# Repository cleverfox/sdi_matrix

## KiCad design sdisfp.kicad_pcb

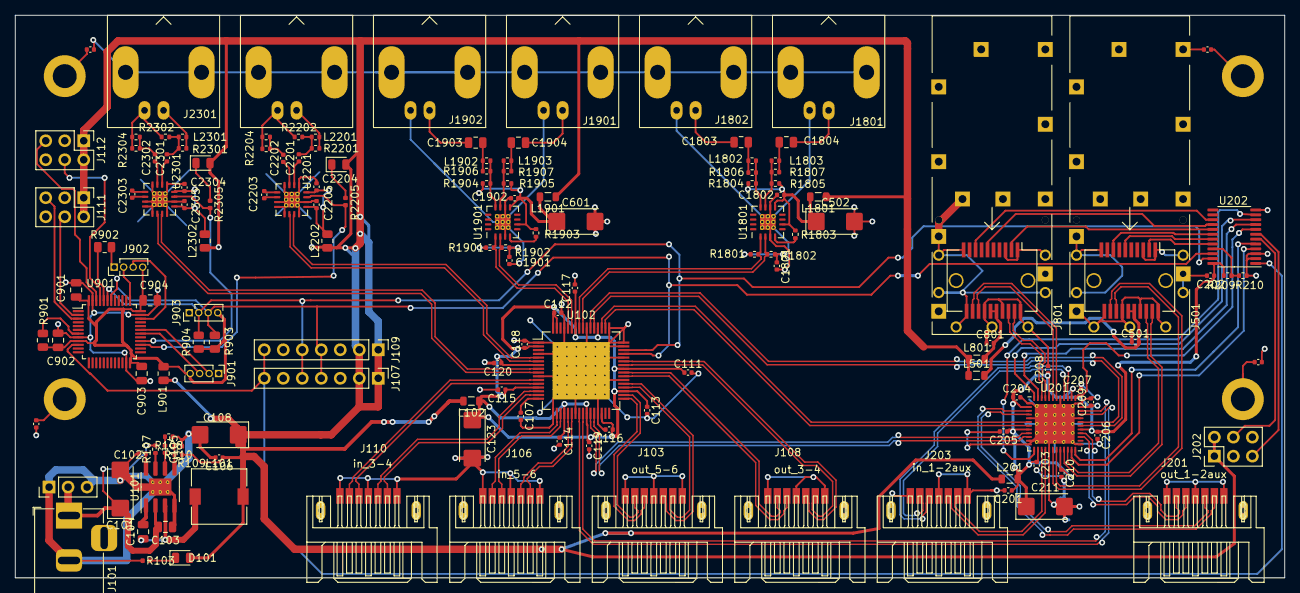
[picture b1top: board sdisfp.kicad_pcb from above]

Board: 2 copper layers, 169.7 x 75.2 mm, 151 parts (0 on the bottom side), 135 nets.

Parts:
C101: C_Polarized_Small; CP_EIA-6032-20_AVX-F_Pad2.25x2.35mm_HandSolder
C102, C106, C107, C111, C112, C113, C114, C115, C116, C117, C118, C119, C120, C203, C204, C205, C206, C207, C208, C209, C210, C501, C801, C1801, C1802, C1901, C1902, C2204, C2205, C2304, C2305: 0.1uF; C_0402_1005Metric
C103: C_Small; C_0805_2012Metric
C104: 10nF; C_0805_2012Metric
C105: 3.9nF; C_0402_1005Metric
C108, C123, C211, C502, C601: 47uF; CP_EIA-6032-20_AVX-F_Pad2.25x2.35mm_HandSolder
C109, C110, C121, C122: C; C_0402_1005Metric
C201, C202: C_Small; C_0402_1005Metric
C901, C902, C903, C904: 0.1uF; C_0805_2012Metric
C1803, C1804, C1903, C1904: 4.7uF; C_0805_2012Metric
C2201, C2202, C2203, C2301, C2302, C2303: 1uF; C_0402_1005Metric
D101: pwr; LED_0805_2012Metric
D2201, D2301: IN_CD; LED_0805_2012Metric
J101: Jack-DC; BarrelJack_Horizontal
J102: Conn_01x03; PinHeader_1x03_P2.54mm_Vertical
J103: out_5-6; SATA-7_SMD
J104, J105, J113, J114: mounting_hole; MountingHole_3.2mm_M3_DIN965_Pad
J106: in_5-6; SATA-7_SMD
J107, J109: ext1; PinHeader_1x07_P2.54mm_Vertical
J108: out_3-4; SATA-7_SMD
J110: in_3-4; SATA-7_SMD
J111: in_5-6aux_pwr; PinHeader_2x03_P2.54mm_Vertical
J112: in_3-4aux_pwr; PinHeader_2x03_P2.54mm_Vertical
J201: out_1-2aux; SATA-7_SMD
J202: in_1-2aux_pwr; PinHeader_2x03_P2.54mm_Vertical
J203: in_1-2aux; SATA-7_SMD
J501: SFP1; Connector_SFP_and_Cage
J801: SFP2; Connector_SFP_and_Cage
J901, J902: SWD; PinHeader_1x04_P1.27mm_Vertical
J903: I2C; PinHeader_1x04_P1.27mm_Vertical
J1801: OUTn7; BNC_Amphenol_B6252HB-NPP3G-50_Horizontal
J1802: OUTp7; BNC_Amphenol_B6252HB-NPP3G-50_Horizontal
J1901: OUTn8; BNC_Amphenol_B6252HB-NPP3G-50_Horizontal
J1902: OUTp8; BNC_Amphenol_B6252HB-NPP3G-50_Horizontal
J2201: IN7; BNC_Amphenol_B6252HB-NPP3G-50_Horizontal
J2301: IN8; BNC_Amphenol_B6252HB-NPP3G-50_Horizontal
L101: 10uH; L_7.3x7.3_H3.5
L102, L201, L501, L801, L1801, L1901: L; L_0805_2012Metric
L901: L; R_0805_2012Metric
L1802, L1803, L1902, L1903, L2201, L2301: 3.9nH; R_0402_1005Metric
L2202, L2302: bead; R_0805_2012Metric
R103, R2205, R2305: 1k; L_0402_1005Metric
R107: 100k; R_0402_1005Metric
R108: 6k8; R_0402_1005Metric
R109: 39k; R_0402_1005Metric
R110: 15k; R_0402_1005Metric
R209: 0; R_0402_1005Metric
R210, R2203, R2303: -; R_0402_1005Metric
R901: R_Small; R_0805_2012Metric
R902: 0; R_0805_2012Metric
R903, R904: 1k; R_0805_2012Metric
R1801, R1802, R1901, R1902: 50; R_0402_1005Metric
R1803, R1903: 750; R_0402_1005Metric
R1804, R1805, R1806, R1807, R1904, R1905, R1906, R1907, R2201, R2202, R2301, R2302: 75; R_0402_1005Metric
R2204, R2304: 37.4; R_0402_1005Metric
U101: MP2307; SOIC-8-1EP_3.9x4.9mm_P1.27mm_EP2.29x3mm_ThermalVias
U102: SN65LVCP408PAPR; TQFP-64-1EP_10x10mm_P0.5mm_EP8x8mm
U201: DS42MB200; QFN-48-1EP_7x7mm_P0.5mm_EP5.3x5.3mm_ThermalVias
U202: PCA9675PW,118; TSSOP-24_4.4x7.8mm_P0.65mm
U901: STM32F100C8Tx; LQFP-48_7x7mm_P0.5mm
U1801, U1901: LMH0303; QFN-16-1EP_4x4mm_P0.65mm_EP2.1x2.1mm_ThermalVias
U2201, U2301: LMH0344; QFN-16-1EP_4x4mm_P0.65mm_EP2.1x2.1mm_ThermalVias

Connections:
+3V3: C106.1, C108.1, D101.2, D2201.2, D2301.2, J107.1, J107.2, J109.1, J109.2, J111.1, J111.2, J112.1, J112.2, J202.1, J202.2, L101.2, L102.2, L201.1, L501.1, L801.1, L901.1, L1801.1, L1901.1, L2202.1, L2302.1, R109.2
/CD3: J112.4, U901.45
/CD4: J112.5, U901.46
/CD5: J111.4, U901.2
/CD6: J111.5, U901.3
/CD7: R2205.2, U901.27, U2201.15
/CD8: R2305.2, U901.28, U2301.15
/INT: J107.7, J109.7, U202.1, U901.10
/MCU/JTCK: J902.2, U901.37
/MCU/JTMS: J902.3, U901.34
/MCU/MCU_VCC: C901.1, C902.1, C903.1, C904.1, J901.4, J902.4, J903.4, L901.2, R901.1, R903.1, R904.1, U901.9, U901.24, U901.36, U901.48
/MCU/RX: J901.2, U901.31
/MCU/TX: J901.3, U901.30
/MTX_VCC: C111.1, C112.1, C113.1, C114.1, C115.1, C116.1, C117.1, C118.1, C119.1, C120.1, C123.1, L102.1, U102.2, U102.7, U102.13, U102.20, U102.26, U102.30, U102.35, U102.41, U102.52, U102.58, U102.63, U102.64
/P1RX+: U102.27, U201.9
/P1RX-: U102.28, U201.10
/P1TX+: U102.54, U201.30
/P1TX-: U102.53, U201.31
/P2RX+: U102.24, U201.33
/P2RX-: U102.25, U201.34
/P2TX+: U102.51, U201.6
/P2TX-: U102.50, U201.7
/P3RX+: J110.2, U102.11
/P3RX-: J110.3, U102.12
/P3TX+: J108.2, U102.40
/P3TX-: J108.3, U102.39
/P4RX+: J110.5, U102.14
/P4RX-: J110.6, U102.15
/P4TX+: J108.5, U102.43
/P4TX-: J108.6, U102.42
/P5RX+: J106.2, U102.18
/P5RX-: J106.3, U102.19
/P5TX+: J103.2, U102.34
/P5TX-: J103.3, U102.33
/P6RX+: J106.5, U102.21
/P6RX-: J106.6, U102.22
/P6TX+: J103.5, U102.37
/P6TX-: J103.6, U102.36
/P7RX+: U102.5, U2201.11
/P7RX-: U102.6, U2201.10
/P7TX+: R1801.2, U102.57, U1801.1
/P7TX-: R1802.1, U102.56, U1801.2
/P8RX+: U102.8, U2301.11
/P8RX-: U102.9, U2301.10
/P8TX+: R1901.2, U102.60, U1901.1
/P8TX-: R1902.1, U102.59, U1901.2
/Ports 1-2/M1VCC: C201.1, C202.1, C203.1, C204.1, C205.1, C206.1, C207.1, C208.1, C209.1, C210.1, C211.1, L201.2, R209.1, U201.2, U201.8, U201.14, U201.20, U201.29, U201.35, U201.38, U201.44, U202.24
/Ports 1-2/MUX_LB0A: U201.47, U202.9
/Ports 1-2/MUX_LB0B: U201.48, U202.10
/Ports 1-2/MUX_LB1A: U201.23, U202.4
/Ports 1-2/MUX_LB1B: U201.24, U202.5
/Ports 1-2/MUX_S0: U201.37, U202.8
/Ports 1-2/MUX_S1: U201.13, U202.11
/Ports 1-2/P1RX+: J203.5, U201.16
/Ports 1-2/P1RX-: J203.6, U201.15
/Ports 1-2/P1TX+: J201.2, U201.28
/Ports 1-2/P1TX-: J201.3, U201.27
/Ports 1-2/P2RX+: J203.2, U201.40
/Ports 1-2/P2RX-: J203.3, U201.39
/Ports 1-2/P2TX+: J201.5, U201.4
/Ports 1-2/P2TX-: J201.6, U201.3
/Ports 1-2/SFP1/RX+: J501.13, U201.19
/Ports 1-2/SFP1/RX-: J501.12, U201.18
/Ports 1-2/SFP1/TX+: J501.18, U201.22
/Ports 1-2/SFP1/TX-: J501.19, U201.21
/Ports 1-2/SFP1FAULT: J501.2, U202.20
/Ports 1-2/SFP1LOS: J501.8, U202.18
/Ports 1-2/SFP1PRES: J501.6, U202.19
/Ports 1-2/SFP2/RX+: J801.13, U201.43
/Ports 1-2/SFP2/RX-: J801.12, U201.42
/Ports 1-2/SFP2/TX+: J801.18, U201.46
/Ports 1-2/SFP2/TX-: J801.19, U201.45
/Ports 1-2/SFP2FAULT: J801.2, U202.17
/Ports 1-2/SFP2LOS: J801.8, U202.15
/Ports 1-2/SFP2PRES: J801.6, U202.16
/Ports 1-2/in1_cd: J202.5, U202.7
/Ports 1-2/in2_cd: J202.4, U202.6
/SCL: J107.4, J109.4, J903.3, R903.2, U102.45, U202.22, U901.42
/SDA: J107.5, J109.5, J903.2, R904.2, U102.46, U202.23, U901.43
/SDI Out 7/CD_VCC: C502.1, C1802.2, L1801.2, R1803.2, R1804.1, R1805.1, U1801.6, U1801.9
/SDI Out 7/SDO+: L1802.1, R1804.2, R1806.2, U1801.12
/SDI Out 7/SDO-: L1803.2, R1805.2, R1807.2, U1801.11
/SDI Out 8/CD_VCC: C601.1, C1902.2, L1901.2, R1903.2, R1904.1, R1905.1, U1901.6, U1901.9
/SDI Out 8/SDO+: L1902.1, R1904.2, R1906.2, U1901.12
/SDI Out 8/SDO-: L1903.2, R1905.2, R1907.2, U1901.11
GND: C101.2, C102.2, C103.2, C106.2, C107.2, C108.2, C109.2, C110.2, C111.2, C112.2, C113.2, C114.2, C115.2, C116.2, C117.2, C118.2, C119.2, C120.2, C121.2, C122.2, C123.2, C201.2, C202.2, C203.2, C204.2, C205.2, C206.2, C207.2, C208.2, C209.2, C210.2, C211.2, C501.1, C502.2, C601.2, C801.1, C901.2, C902.2, C903.2, C904.2, C1801.2, C1802.1, C1901.2, C1902.1, C2204.2, C2205.2, C2304.2, C2305.2, J101.2, J102.1, J102.3, J103.1, J103.4, J103.7, J106.1, J106.4, J106.7, J107.3, J107.6, J108.1, J108.4, J108.7, J109.3, J109.6, J110.1, J110.4, J110.7, J111.3, J111.6, J112.3, J112.6, J201.1, J201.4, J201.7, J202.3, J202.6, J203.1, J203.4, J203.7, J501.1, J501.3, J501.10, J501.11, J501.14, J501.17, J501.20, J501.CAGE, J801.1, J801.3, J801.10, J801.11, J801.14, J801.17, J801.20, J801.CAGE, J901.1, J902.1, J903.1, J1801.2, J1802.2, J1901.2, J1902.2, J2201.2, J2301.2, R103.2, R108.1, R110.1, R210.2, R902.2, R2202.2, R2203.1, R2204.2, R2302.2, R2303.1, R2304.2, U101.4, U101.9, U102.1, U102.4, U102.10, U102.17, U102.23, U102.29, U102.38, U102.44, U102.47, U102.48, U102.49, U102.55, U102.61, U102.65, U201.1, U201.5, U201.11, U201.12, U201.17, U201.25, U201.32, U201.36, U201.41, U201.49, U202.2, U202.3, U202.12, U901.8, U901.23, U901.35, U901.47, U1801.3, U1801.10, U1801.17, U1901.3, U1901.10, U1901.17, U2201.1, U2201.4, U2201.7, U2201.8, U2201.9, U2201.12, U2201.14, U2201.17, U2301.1, U2301.4, U2301.7, U2301.8, U2301.9, U2301.12, U2301.14, U2301.17
unnamed: C101.1, C103.1, J101.1, J102.2, R107.2, U101.2
unnamed: C102.1, U101.8
unnamed: C104.1, L101.1, U101.3
unnamed: C104.2, U101.1
unnamed: C105.1, R108.2
unnamed: C105.2, U101.6
unnamed: C107.1, U102.16
unnamed: C109.1, J104.1
unnamed: C110.1, J105.1
unnamed: C121.1, J113.1
unnamed: C122.1, J114.1
unnamed: C501.2, J501.15, J501.16, L501.2
unnamed: C801.2, J801.15, J801.16, L801.2
unnamed: C1801.1, R1801.1, R1802.2
unnamed: C1803.1, L1802.2, R1806.1
unnamed: C1803.2, J1802.1
unnamed: C1804.1, L1803.1, R1807.1
unnamed: C1804.2, J1801.1
unnamed: C1901.1, R1901.1, R1902.2
unnamed: C1903.1, L1902.2, R1906.1
unnamed: C1903.2, J1902.1
unnamed: C1904.1, L1903.1, R1907.1
unnamed: C1904.2, J1901.1
unnamed: C2201.1, U2201.2
unnamed: C2201.2, L2201.2, R2201.1, R2202.1
unnamed: C2202.1, U2201.3
unnamed: C2202.2, R2203.2, R2204.1
unnamed: C2203.1, U2201.5
unnamed: C2203.2, U2201.6
unnamed: C2204.1, C2205.1, L2202.2, U2201.13, U2201.16
unnamed: C2301.1, U2301.2
unnamed: C2301.2, L2301.2, R2301.1, R2302.1
unnamed: C2302.1, U2301.3
unnamed: C2302.2, R2303.2, R2304.1
unnamed: C2303.1, U2301.5
unnamed: C2303.2, U2301.6
unnamed: C2304.1, C2305.1, L2302.2, U2301.13, U2301.16
unnamed: D101.1, R103.1
unnamed: D2201.1, R2205.1
unnamed: D2301.1, R2305.1
unnamed: J2201.1, L2201.1, R2201.2
unnamed: J2301.1, L2301.1, R2301.2
unnamed: R107.1, U101.7
unnamed: R109.1, R110.2, U101.5
unnamed: R209.2, R210.1, U202.21
unnamed: R901.2, U901.7
unnamed: R902.1, U901.44
unnamed: R1803.1, U1801.4
unnamed: R1903.1, U1901.4

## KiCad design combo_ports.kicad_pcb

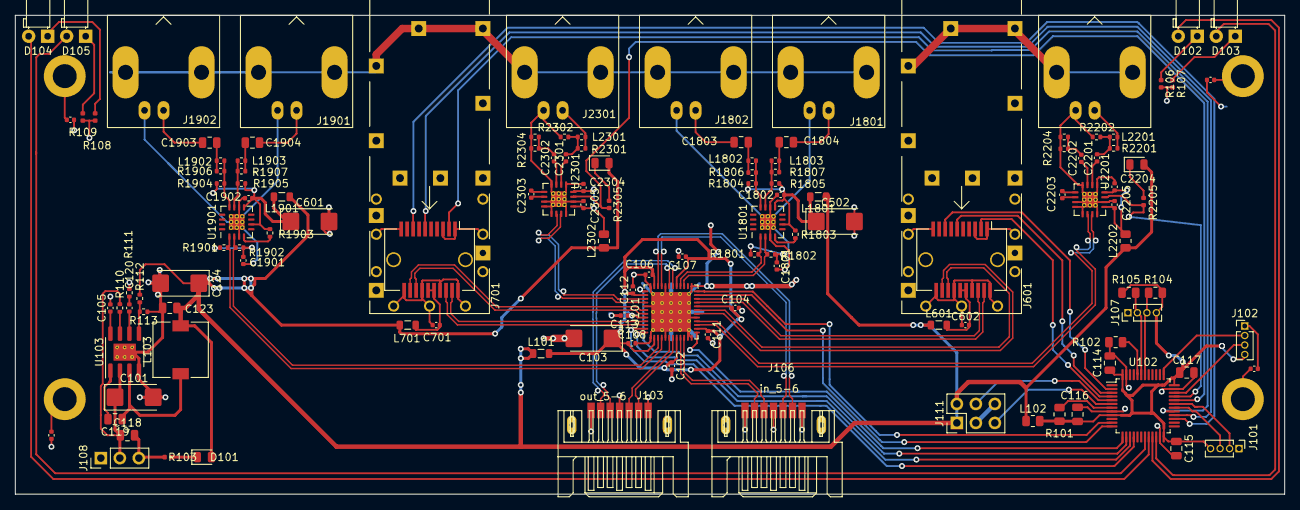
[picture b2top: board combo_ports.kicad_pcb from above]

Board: 2 copper layers, 169.7 x 64.0 mm, 131 parts (0 on the bottom side), 111 nets.

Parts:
C101: C_Polarized_Small; CP_EIA-6032-20_AVX-F_Pad2.25x2.35mm_HandSolder
C102, C104, C105, C106, C107, C108, C111, C602, C701, C1801, C1802, C1901, C1902, C2204, C2205, C2304, C2305: 0.1uF; C_0402_1005Metric
C103, C124, C502, C601: 47uF; CP_EIA-6032-20_AVX-F_Pad2.25x2.35mm_HandSolder
C109, C110, C121, C122: C; C_0402_1005Metric
C112, C113: C_Small; C_0402_1005Metric
C114, C115, C116, C117, C123: 0.1uF; C_0805_2012Metric
C118: C_Small; C_0805_2012Metric
C119: 10nF; C_0805_2012Metric
C120: 3.9nF; C_0402_1005Metric
C1803, C1804, C1903, C1904: 4.7uF; C_0805_2012Metric
C2201, C2202, C2203, C2301, C2302, C2303: 1uF; C_0402_1005Metric
D101: pwr; LED_0805_2012Metric
D102: P2SFP; LED_D3.0mm_Horizontal_O1.27mm_Z2.0mm
D103: P2SDI; LED_D3.0mm_Horizontal_O1.27mm_Z2.0mm
D104: P1SFP; LED_D3.0mm_Horizontal_O1.27mm_Z2.0mm
D105: P1SDI; LED_D3.0mm_Horizontal_O1.27mm_Z2.0mm
D2201, D2301: IN_CD; LED_0805_2012Metric
J101, J102: SWD; PinHeader_1x04_P1.27mm_Vertical
J103: out_5-6; SATA-7_SMD
J104, J105, J113, J114: mounting_hole; MountingHole_3.2mm_M3_DIN965_Pad
J106: in_5-6; SATA-7_SMD
J107: I2C; PinHeader_1x04_P1.27mm_Vertical
J108: Conn_01x03; PinHeader_1x03_P2.54mm_Vertical
J111: in_5-6aux_pwr; PinHeader_2x03_P2.54mm_Vertical
J601: SFP1; Connector_SFP_and_Cage
J701: SFP2; Connector_SFP_and_Cage
J1801: OUTn7; BNC_Amphenol_B6252HB-NPP3G-50_Horizontal
J1802: OUTp7; BNC_Amphenol_B6252HB-NPP3G-50_Horizontal
J1901: OUTn8; BNC_Amphenol_B6252HB-NPP3G-50_Horizontal
J1902: OUTp8; BNC_Amphenol_B6252HB-NPP3G-50_Horizontal
J2201: IN7; BNC_Amphenol_B6252HB-NPP3G-50_Horizontal
J2301: IN8; BNC_Amphenol_B6252HB-NPP3G-50_Horizontal
L101, L601, L701, L1801, L1901: L; L_0805_2012Metric
L102: L; R_0805_2012Metric
L103: 10uH; L_7.3x7.3_H3.5
L1802, L1803, L1902, L1903, L2201, L2301: 3.9nH; R_0402_1005Metric
L2202, L2302: bead; R_0805_2012Metric
R101: R_Small; R_0805_2012Metric
R102: 0; R_0805_2012Metric
R103, R106, R107, R108, R109, R2205, R2305: 1k; L_0402_1005Metric
R104, R105: 1k; R_0805_2012Metric
R110: 100k; R_0402_1005Metric
R111: 6k8; R_0402_1005Metric
R112: 39k; R_0402_1005Metric
R113: 15k; R_0402_1005Metric
R1801, R1802, R1901, R1902: 50; R_0402_1005Metric
R1803, R1903: 750; R_0402_1005Metric
R1804, R1805, R1806, R1807, R1904, R1905, R1906, R1907, R2201, R2202, R2301, R2302: 75; R_0402_1005Metric
R2203, R2303: -; R_0402_1005Metric
R2204, R2304: 37.4; R_0402_1005Metric
U101: DS42MB200; QFN-48-1EP_7x7mm_P0.5mm_EP5.3x5.3mm_ThermalVias
U102: STM32F100C8Tx; LQFP-48_7x7mm_P0.5mm
U103: MP2307; SOIC-8-1EP_3.9x4.9mm_P1.27mm_EP2.29x3mm_ThermalVias
U1801, U1901: LMH0303; QFN-16-1EP_4x4mm_P0.65mm_EP2.1x2.1mm_ThermalVias
U2201, U2301: LMH0344; QFN-16-1EP_4x4mm_P0.65mm_EP2.1x2.1mm_ThermalVias

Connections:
+3V3: C123.1, C124.1, D101.2, D2201.2, D2301.2, J111.1, J111.2, L101.1, L102.1, L103.2, L601.1, L701.1, L1801.1, L1901.1, L2202.1, L2302.1, R112.2
/CD5: R2205.2, U102.33, U2201.15
/CD6: R2305.2, U102.32, U2301.15
/JTCK: J102.2, U102.37
/JTMS: J102.3, U102.34
/M1VCC: C102.1, C103.1, C104.1, C106.1, C107.1, C108.1, C111.1, C112.1, C113.1, L101.2, U101.2, U101.8, U101.14, U101.20, U101.29, U101.35, U101.38, U101.44
/MCD5: J111.4, U102.5
/MCD6: J111.5, U102.6
/MCU_VCC: C114.1, C115.1, C116.1, C117.1, J101.4, J102.4, J107.4, L102.2, R101.1, R104.1, R105.1, U102.9, U102.24, U102.36, U102.48
/MUX_LB0A: U101.47, U102.16
/MUX_LB0B: U101.48, U102.15
/MUX_LB1A: U101.23, U102.12
/MUX_LB1B: U101.24, U102.11
/MUX_S0: U101.37, U102.14
/MUX_S1: U101.13, U102.13
/P1RX+: U101.16, U2201.11
/P1RX-: U101.15, U2201.10
/P1TX+: R1801.2, U101.28, U1801.1
/P1TX-: R1802.1, U101.27, U1801.2
/P2RX+: U101.40, U2301.11
/P2RX-: U101.39, U2301.10
/P2TX+: R1901.2, U101.4, U1901.1
/P2TX-: R1902.1, U101.3, U1901.2
/RX: J101.2, U102.31
/RX1+: J106.2, U101.9
/RX1-: J106.3, U101.10
/RX2+: J106.5, U101.33
/RX2-: J106.6, U101.34
/SCL: J107.3, R104.2, U102.42
/SDA: J107.2, R105.2, U102.43
/SDI1CD: D105.2, U102.19
/SDI2CD: D102.2, U102.21
/SDI Out 5/CD_VCC: C502.1, C1802.2, L1801.2, R1803.2, R1804.1, R1805.1, U1801.6, U1801.9
/SDI Out 5/SDO+: L1802.1, R1804.2, R1806.2, U1801.12
/SDI Out 5/SDO-: L1803.2, R1805.2, R1807.2, U1801.11
/SDI Out 6/CD_VCC: C601.1, C1902.2, L1901.2, R1903.2, R1904.1, R1905.1, U1901.6, U1901.9
/SDI Out 6/SDO+: L1902.1, R1904.2, R1906.2, U1901.12
/SDI Out 6/SDO-: L1903.2, R1905.2, R1907.2, U1901.11
/SFP1CD: D104.2, U102.20
/SFP1FAULT: J601.2, U102.4
/SFP1LOS: J601.8, U102.2
/SFP1PRES: J601.6, U102.3
/SFP2CD: D103.2, U102.22
/SFP2FAULT: J701.2, U102.29
/SFP2LOS: J701.8, U102.27
/SFP2PRES: J701.6, U102.28
/TX: J101.3, U102.30
/TX1+: J103.2, U101.30
/TX1-: J103.3, U101.31
/TX2+: J103.5, U101.6
/TX2-: J103.6, U101.7
/sfp5/RX+: J601.13, U101.19
/sfp5/RX-: J601.12, U101.18
/sfp5/SFPVCC: C602.2, J601.15, J601.16, L601.2
/sfp5/TX+: J601.18, U101.22
/sfp5/TX-: J601.19, U101.21
/sfp6/RX+: J701.13, U101.43
/sfp6/RX-: J701.12, U101.42
/sfp6/SFPVCC: C701.2, J701.15, J701.16, L701.2
/sfp6/TX+: J701.18, U101.46
/sfp6/TX-: J701.19, U101.45
GND: C101.2, C102.2, C103.2, C104.2, C105.2, C106.2, C107.2, C108.2, C109.2, C110.2, C111.2, C112.2, C113.2, C114.2, C115.2, C116.2, C117.2, C118.2, C121.2, C122.2, C123.2, C124.2, C502.2, C601.2, C602.1, C701.1, C1801.2, C1802.1, C1901.2, C1902.1, C2204.2, C2205.2, C2304.2, C2305.2, J101.1, J102.1, J103.1, J103.4, J103.7, J106.1, J106.4, J106.7, J107.1, J108.1, J108.3, J111.3, J111.6, J601.1, J601.3, J601.10, J601.11, J601.14, J601.17, J601.20, J601.CAGE, J701.1, J701.3, J701.10, J701.11, J701.14, J701.17, J701.20, J701.CAGE, J1801.2, J1802.2, J1901.2, J1902.2, J2201.2, J2301.2, R102.2, R103.2, R106.2, R107.2, R108.2, R109.2, R111.1, R113.1, R2202.2, R2203.1, R2204.2, R2302.2, R2303.1, R2304.2, U101.1, U101.5, U101.11, U101.12, U101.17, U101.25, U101.32, U101.36, U101.41, U101.49, U102.8, U102.23, U102.35, U102.47, U103.4, U103.9, U1801.3, U1801.10, U1801.17, U1901.3, U1901.10, U1901.17, U2201.1, U2201.4, U2201.7, U2201.8, U2201.9, U2201.12, U2201.14, U2201.17, U2301.1, U2301.4, U2301.7, U2301.8, U2301.9, U2301.12, U2301.14, U2301.17
unnamed: C101.1, C118.1, J108.2, R110.2, U103.2
unnamed: C105.1, U103.8
unnamed: C109.1, J104.1
unnamed: C110.1, J105.1
unnamed: C119.1, L103.1, U103.3
unnamed: C119.2, U103.1
unnamed: C120.1, R111.2
unnamed: C120.2, U103.6
unnamed: C121.1, J113.1
unnamed: C122.1, J114.1
unnamed: C1801.1, R1801.1, R1802.2
unnamed: C1803.1, L1802.2, R1806.1
unnamed: C1803.2, J1802.1
unnamed: C1804.1, L1803.1, R1807.1
unnamed: C1804.2, J1801.1
unnamed: C1901.1, R1901.1, R1902.2
unnamed: C1903.1, L1902.2, R1906.1
unnamed: C1903.2, J1902.1
unnamed: C1904.1, L1903.1, R1907.1
unnamed: C1904.2, J1901.1
unnamed: C2201.1, U2201.2
unnamed: C2201.2, L2201.2, R2201.1, R2202.1
unnamed: C2202.1, U2201.3
unnamed: C2202.2, R2203.2, R2204.1
unnamed: C2203.1, U2201.5
unnamed: C2203.2, U2201.6
unnamed: C2204.1, C2205.1, L2202.2, U2201.13, U2201.16
unnamed: C2301.1, U2301.2
unnamed: C2301.2, L2301.2, R2301.1, R2302.1
unnamed: C2302.1, U2301.3
unnamed: C2302.2, R2303.2, R2304.1
unnamed: C2303.1, U2301.5
unnamed: C2303.2, U2301.6
unnamed: C2304.1, C2305.1, L2302.2, U2301.13, U2301.16
unnamed: D101.1, R103.1
unnamed: D102.1, R106.1
unnamed: D103.1, R107.1
unnamed: D104.1, R108.1
unnamed: D105.1, R109.1
unnamed: D2201.1, R2205.1
unnamed: D2301.1, R2305.1
unnamed: J2201.1, L2201.1, R2201.2
unnamed: J2301.1, L2301.1, R2301.2
unnamed: R101.2, U102.7
unnamed: R102.1, U102.44
unnamed: R110.1, U103.7
unnamed: R112.1, R113.2, U103.5
unnamed: R1803.1, U1801.4
unnamed: R1903.1, U1901.4

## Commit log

2021-01-05 initital commit
